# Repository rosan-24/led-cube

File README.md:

# led-cube
4x4x4 led cube powered by esp32
Hello

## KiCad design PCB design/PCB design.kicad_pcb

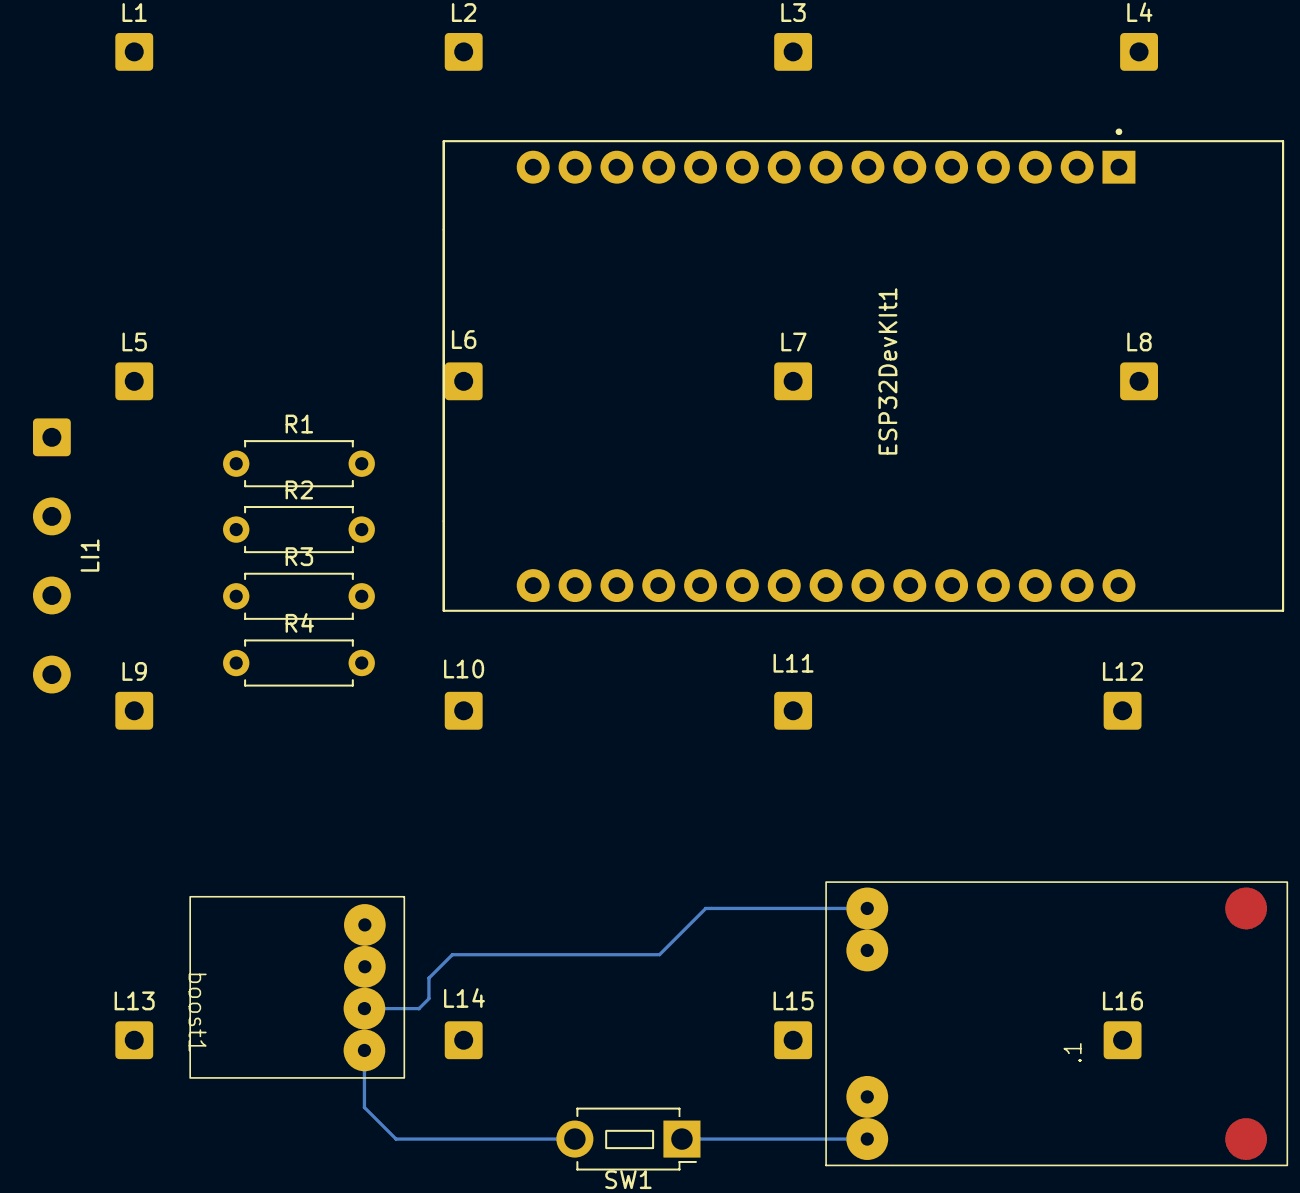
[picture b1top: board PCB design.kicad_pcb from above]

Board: 2 copper layers, 25 parts (0 on the bottom side), 7 nets.

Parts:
.1: TP4056
ESP32DevKIt1: ESP32DevKit; MODULE_ESP32_DEVKIT_V1
L1, L2, L3, L4, L5, L6, L7, L8, L9, L10, L11, L12, L13, L14, L15, L16: Conn_01x01; SolderWire-0.5sqmm_1x01_D0.9mm_OD2.3mm
LI1: Conn_01x04; SolderWire-0.5sqmm_1x04_P4.8mm_D0.9mm_OD2.3mm
R1, R2, R3, R4: 220; R_Axial_DIN0207_L6.3mm_D2.5mm_P7.62mm_Horizontal
SW1: SW_SPST; SW_PUSH_1P1T_6x3.5mm_H5.0_APEM_MJTP1250
boost1: 7semi tps61023; 7Semi Tps61023

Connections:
unnamed: .1.4 (out+), SW1.1 (A)
unnamed: .1.1 (out-), boost1.3 (GND)
unnamed: LI1.1, R1.1
unnamed: LI1.2, R2.1
unnamed: LI1.3, R3.1
unnamed: LI1.4, R4.1
unnamed: SW1.2 (B), boost1.4 (VIN)
